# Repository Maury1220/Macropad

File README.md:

# Streamdeck copy kinda???

Hello this is my copy of a streamdeck that can do shortcuts, hotkeys, and maybe like a soundboard maybe later.

# Devlog #1 

My frist devlog is just the schematic of the pcb however maybe I might cange a few things but right now its fine. mybey colume control may benfit me in some way however im not sure

# Devlog #2

i managed to do many things today. for starters I was able to model the pcb of the actual schematic and I did eventually add a rotary encoder for volume control however this was a pain in the butt because to figure out how the rotary encoder should connect to the seed studio. anyways, I did also make the 3d model of the cade that the board would fit into and at the time of writing this its cirrently printing on my 3d printer.

# Devlog #3

no image today but the case came out looking great but i think i mesured the pcb wrong because it looked a little small for hot sawp switches to fit but I dont know. Also I managed to get the code in a beta but I have no idea how to code and I am still looking at learning about that so I asked the github guy for help 

# Devlog #4

I have now finished everything needed to puch my first project!! Above it the final parts for the the building faze of my macrodeck.

# if you wanna copy here is a Setup Guide

## Setup

1. Copy `main.py` onto your RP2040 board running CircuitPython.
2. Adjust `KEY_PINS`, encoder pins, and `KEY_ACTIVE_HIGH` in `main.py` to match your wiring.
3. Install PySerial and Keyboard on your PC:

```bash
python -m pip install pyserial
```

```bash
python -m pip install keyboard
```

4. Run the host UI:

```bash
python host_ui.py
```

## Host UI commands

- `s`: request current state
- `r`: reset encoder position
- `d`: toggle debug reporting
- `h`: show help
- `q`: quit

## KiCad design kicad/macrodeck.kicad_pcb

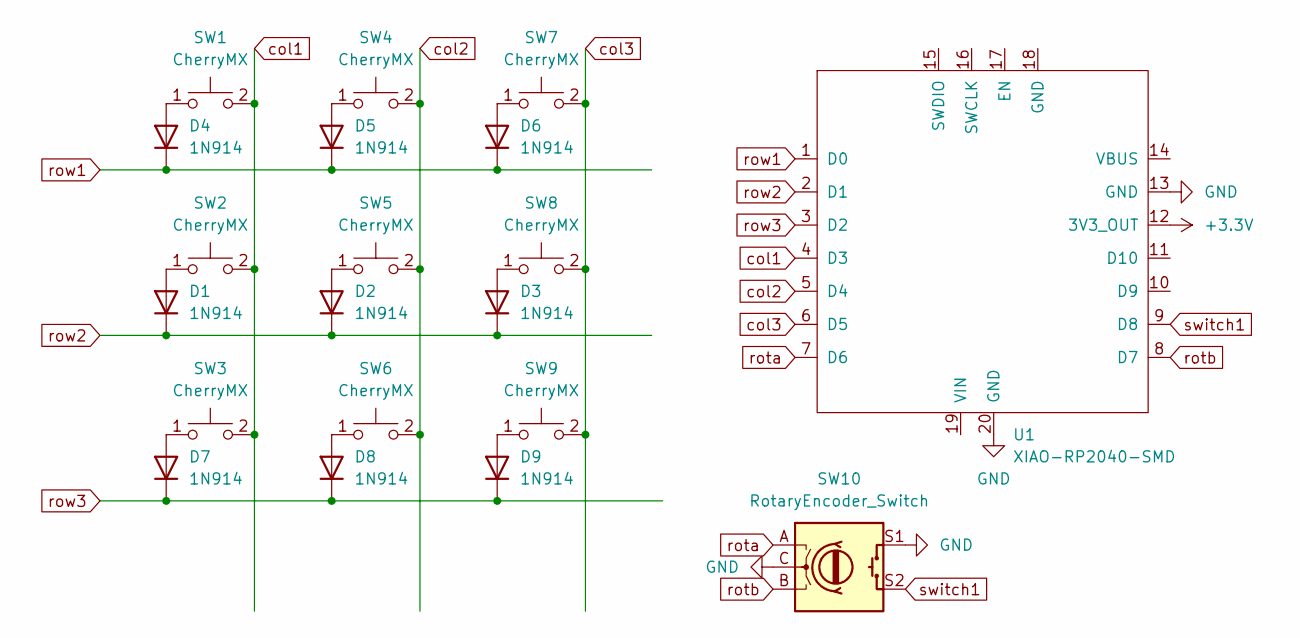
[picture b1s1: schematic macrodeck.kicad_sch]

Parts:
D1, D2, D3, D4, D5, D6, D7, D8, D9: 1N914; D_DO-35_SOD27_P7.62mm_Horizontal
SW1, SW2, SW3, SW4, SW5, SW6, SW7, SW8, SW9: CherryMX; CPG151101S11_1.00u_PCB
SW10: RotaryEncoder_Switch; RotaryEncoder_Alps_EC11E-Switch_Vertical_H20mm_MountingHoles
U1: XIAO-RP2040-SMD

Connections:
+3.3V: U1.12 (3V3_OUT)
GND: SW10.C, SW10.S1, U1.13 (GND), U1.20 (GND)
unnamed: D1.2 (A), SW2.1
unnamed: D2.2 (A), SW5.1
unnamed: D3.2 (A), SW8.1
unnamed: D4.2 (A), SW1.1
unnamed: D5.2 (A), SW4.1
unnamed: D6.2 (A), SW7.1
unnamed: D7.2 (A), SW3.1
unnamed: D8.2 (A), SW6.1
unnamed: D9.2 (A), SW9.1
col1: SW1.2, SW2.2, SW3.2, U1.4 (D3)
col2: SW4.2, SW5.2, SW6.2, U1.5 (D4)
col3: SW7.2, SW8.2, SW9.2, U1.6 (D5)
rota: SW10.A, U1.7 (D6)
rotb: SW10.B, U1.8 (D7)
row1: D4.1 (K), D5.1 (K), D6.1 (K), U1.1 (D0)
row2: D1.1 (K), D2.1 (K), D3.1 (K), U1.2 (D1)
row3: D7.1 (K), D8.1 (K), D9.1 (K), U1.3 (D2)
switch1: SW10.S2, U1.9 (D8)

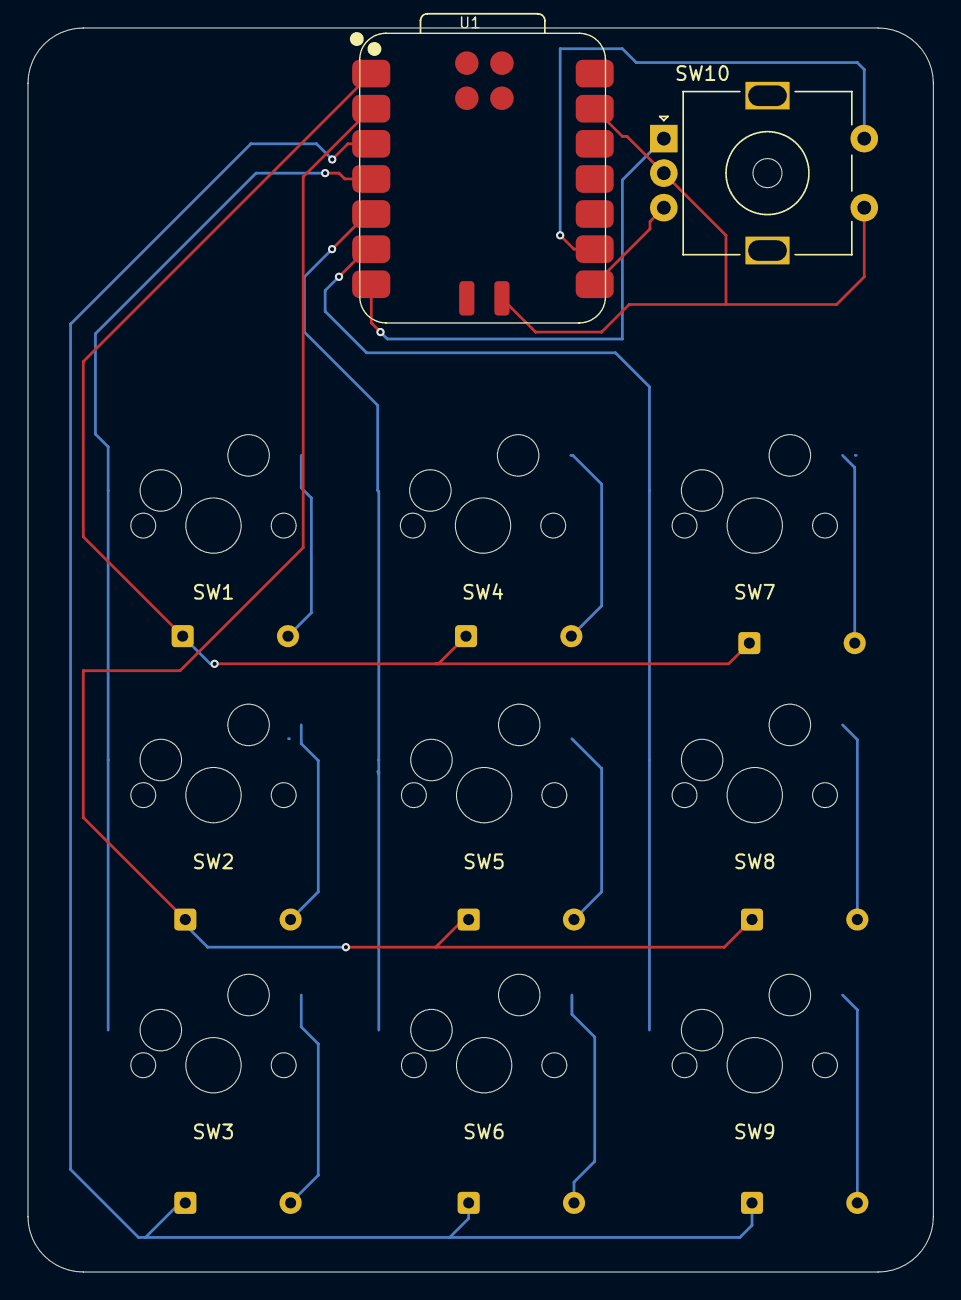
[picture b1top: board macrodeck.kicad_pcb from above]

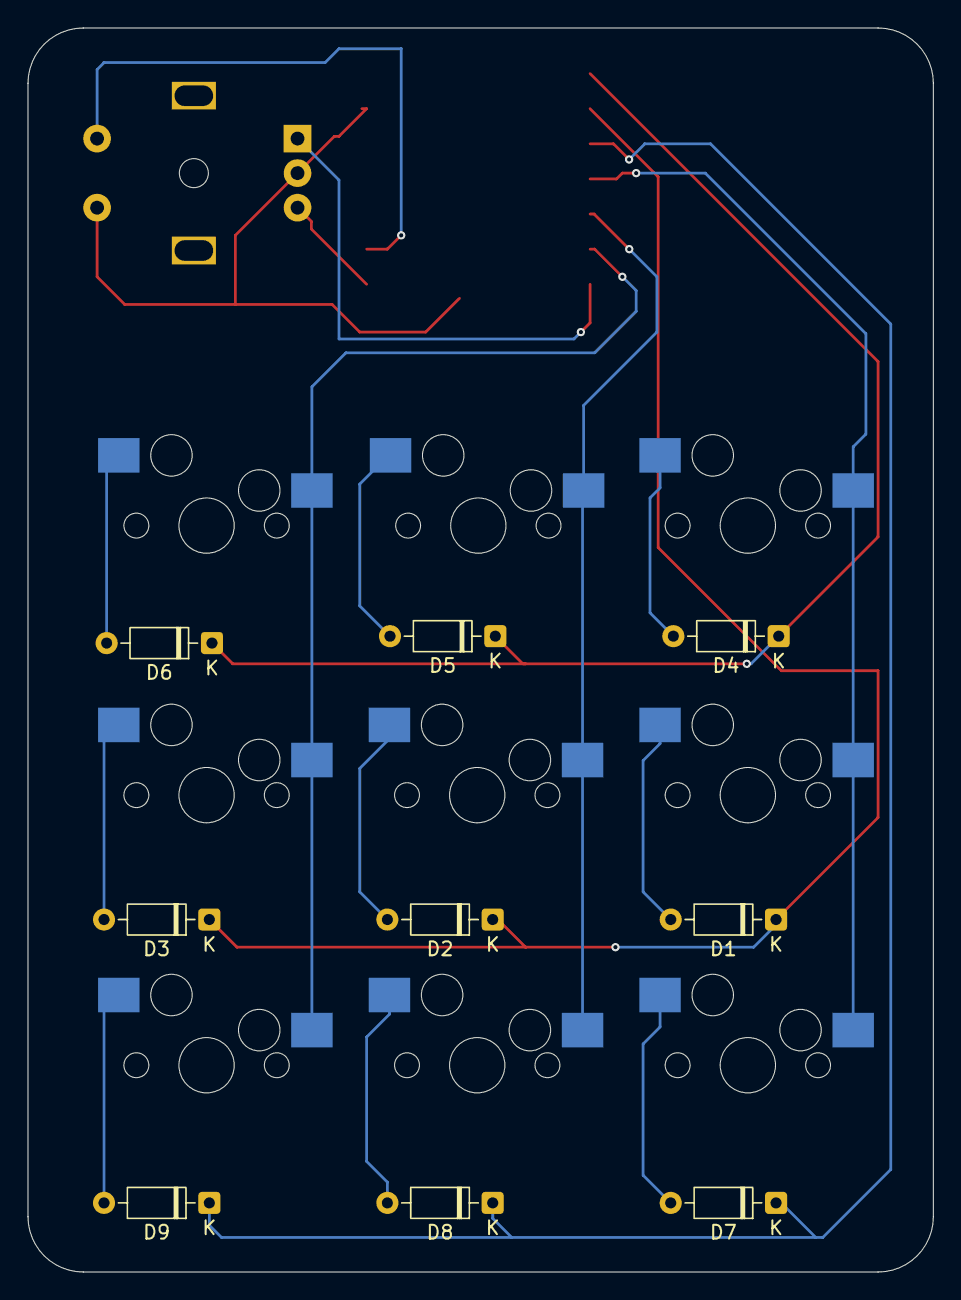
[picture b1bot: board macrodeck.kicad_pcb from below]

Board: 2 copper layers, 65.5 x 90.0 mm, 20 parts (9 on the bottom side), 19 nets.

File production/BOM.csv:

"Id";"Designator";"Footprint";"Quantity";"Designation";"Supplier and ref";
1;"D1, D2, D3, D4, D5, D6, D7, D8, D9";"D_DO-35_SOD27_P7.62mm_Horizontal";9;"1N914";;;
2;"SW1, SW2, SW3, SW4, SW5, SW6, SW7, SW8, SW9";"CPG151101S11_1.00u_PCB";9;"CherryMX";;;
3;"SW10";"RotaryEncoder_Alps_EC11E-Switch_Vertical_H20mm_MountingHoles";1;"RotaryEncoder_Switch";;;
4;"U1";"XIAO-RP2040-SMD";1;"XIAO-RP2040-SMD";;;
